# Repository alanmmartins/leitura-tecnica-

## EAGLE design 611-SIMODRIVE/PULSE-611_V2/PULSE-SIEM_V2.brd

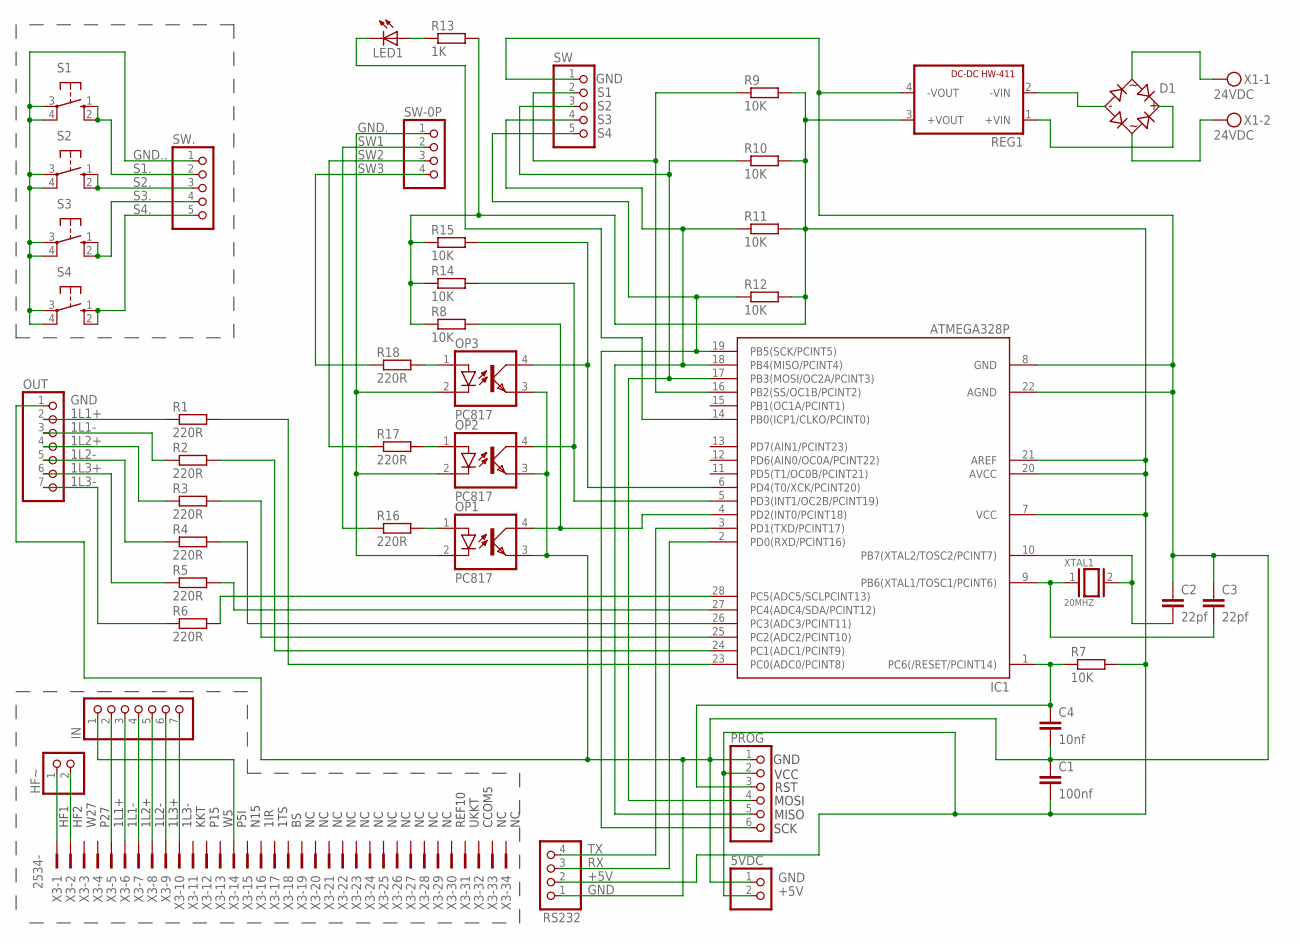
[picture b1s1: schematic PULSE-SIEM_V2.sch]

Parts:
5VDC: PINHD-1X2; 1X02
C1: 100nf; C050-025X075
C2, C3: 22pf; C25-024X044
C4: 10nf; C050-025X075
D1: S1WBS80
HF~: PINHD-1X2; 1X02
IC1: ATMEGA328P; DIL28-3
IN: PINHD-1X7; 1X07
LED1: LED; LED_5MM
OP1, OP2, OP3: PC817; DIL04
OUT: PINHD-1X7; 1X07
PROG: ICSP-AVR-6-PIN
R1, R2, R3, R4, R5, R6, R16, R17, R18: 220R; RESISTOR_1/4_7.5
R7, R8, R9, R10, R11, R12, R14, R15: 10K; RESISTOR_1/4_7.5
R13: 1K; RESISTOR_1/4_7.5
REG1: LM2596_DC-DC_HW-411
RS232: PINHD-1X4; 1X04
S1, S2, S3, S4: 10-XX; B3F-10XX
SW, SW.: PINHD-1X5; 1X05
SW-0P: PINHD-1X4; 1X04
X1: 24VDC; MKDSN1,5/2-5,08
X3: 2534-; PAK100/2500-34
XTAL1: 20MHZ; QS

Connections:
1L1+: OUT.2, R1.1
1L1-: OUT.3, R2.1
1L2+: OUT.4, R3.1
1L2-: OUT.5, R4.1
1L3+: OUT.6, R5.1
1L3-: OUT.7, R6.1
+5V: 5VDC.2, C1.2, IC1.7 (VCC), IC1.20 (AVCC), IC1.21 (AREF), PROG.2 (VCC), R7.2, R8.1, R9.2, R10.2, R11.2, R12.2, R13.2, R14.1, R15.1, REG1.3 (+VOUT), RS232.2
GND: 5VDC.1, C1.1, C2.1, C3.1, C4.2, IC1.8 (GND), IC1.22 (AGND), OP1.3 (EMIT), OP2.3 (EMIT), OP3.3 (EMIT), OUT.1, PROG.1 (GND), REG1.4 (-VOUT), RS232.1, SW.1
GND.: OP1.2 (C), OP2.2 (C), OP3.2 (C), SW-0P.1
GND..: S1.3, S1.4 (P1), S2.3, S2.4 (P1), S3.3, S3.4 (P1), S4.3, S4.4 (P1), SW..1
unnamed: IC1.4 (PD2(INT0/PCINT18)), OP1.4 (COL), R8.2
unnamed: IC1.5 (PD3(INT1/OC2B/PCINT19)), OP2.4 (COL), R14.2
unnamed: IC1.6 (PD4(T0/XCK/PCINT20)), OP3.4 (COL), R15.2
unnamed: OP1.1 (A), R16.2
unnamed: OP2.1 (A), R17.2
unnamed: OP3.1 (A), R18.2
unnamed: HF~.1, X3.1
unnamed: IN.2, X3.5
unnamed: C2.2, IC1.10 (PB7(XTAL2/TOSC2/PCINT7)), XTAL1.2
unnamed: C4.1, IC1.1 (PC6(/RESET/PCINT14)), PROG.3 (RST), R7.1
unnamed: C3.2, IC1.9 (PB6(XTAL1/TOSC1/PCINT6)), XTAL1.1
unnamed: HF~.2, X3.2
unnamed: IC1.23 (PC0(ADC0/PCINT8)), R1.2
unnamed: IC1.24 (PC1(ADC1/PCINT9)), R2.2
unnamed: IC1.25 (PC2(ADC2/PCINT10)), R3.2
unnamed: IC1.26 (PC3(ADC3/PCINT11)), R4.2
unnamed: IC1.27 (PC4(ADC4/SDA/PCINT12)), R5.2
unnamed: IC1.28 (PC5(ADC5/SCLPCINT13)), R6.2
unnamed: IN.3, X3.6
unnamed: IN.4, X3.7
unnamed: IN.5, X3.8
unnamed: IC1.14 (PB0(ICP1/CLKO/PCINT0)), LED1.K (C)
unnamed: LED1.A, R13.1
unnamed: IN.6, X3.9
unnamed: IN.7, X3.10
unnamed: IN.1, X3.14
unnamed: D1.~ (AC1), X1.1
unnamed: D1.~~ (AC2), X1.2
unnamed: D1.-, REG1.2 (-VIN)
unnamed: D1.+, REG1.1 (+VIN)
RX: IC1.2 (PD0(RXD/PCINT16)), RS232.3
S1: IC1.16 (PB2(SS/OC1B/PCINT2)), R9.1, SW.2
S1.: S1.1 (S), S1.2 (S1), SW..2
S2: IC1.17 (PB3(MOSI/OC2A/PCINT3)), PROG.4 (MOSI), R10.1, SW.3
S2.: S2.1 (S), S2.2 (S1), SW..3
S3: IC1.18 (PB4(MISO/PCINT4)), PROG.5 (MISO), R11.1, SW.4
S3.: S3.1 (S), S3.2 (S1), SW..4
S4: IC1.19 (PB5(SCK/PCINT5)), PROG.6 (SCK), R12.1, SW.5
S4.: S4.1 (S), S4.2 (S1), SW..5
SW1: R16.1, SW-0P.2
SW2: R17.1, SW-0P.3
SW3: R18.1, SW-0P.4
TX: IC1.3 (PD1(TXD/PCINT17)), RS232.4

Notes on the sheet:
HF1 HF2 W27 P27 1L1+ 1L1- 1L2+ 1L2- 1L3+ 1L3- KKT P15 W5 P5I N15 1IR 1TS BS NC NC NC NC NC NC NC NC NC NC NC REF10 UKKT CCOM5 NC NC

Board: 2 copper layers, 45 parts (0 on the bottom side), 53 nets, no tracks yet.

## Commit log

2025-04-28 upload pdf
2025-04-28 memorias upload
2025-04-28 611 upload
2025-04-28 eprons upload
2025-04-29 datasheet upload
